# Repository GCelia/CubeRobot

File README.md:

# CubeRobot
Projet qui permet d'apprendre le routage sur Kicad ainsi que de coder sur platformIO en C

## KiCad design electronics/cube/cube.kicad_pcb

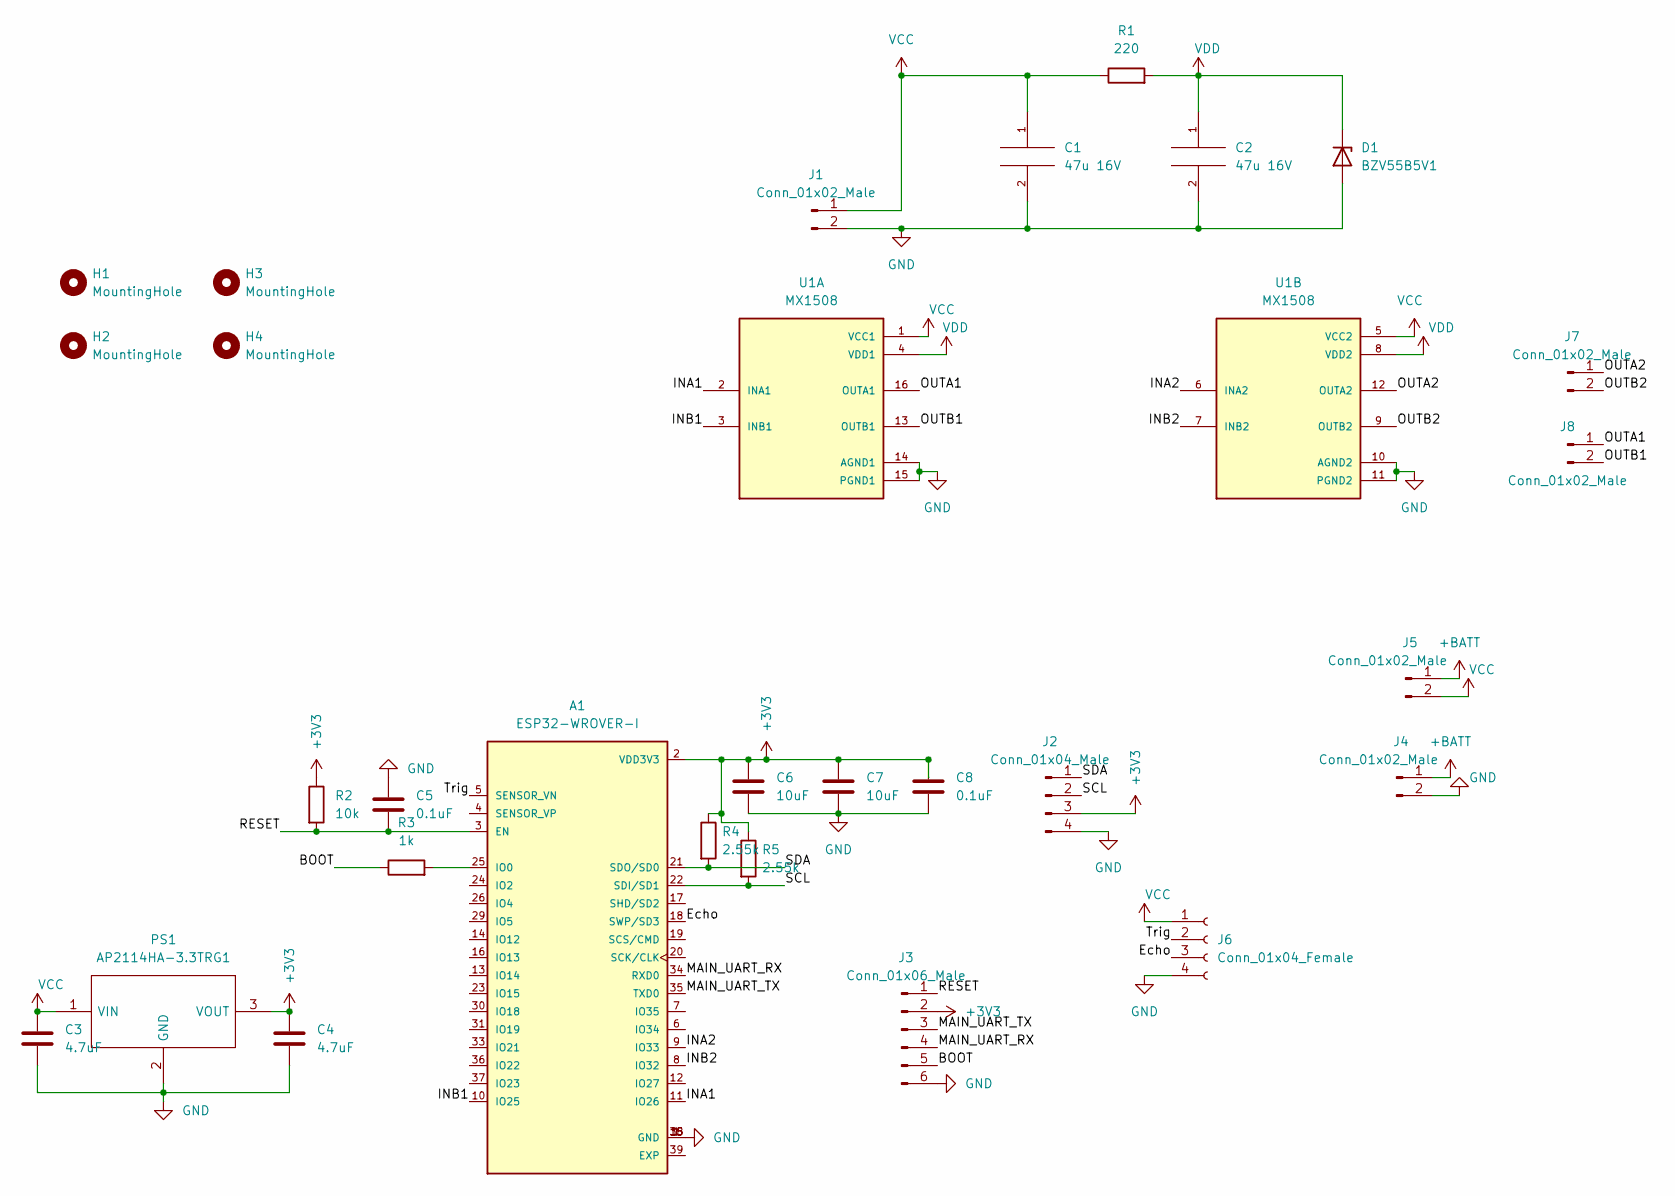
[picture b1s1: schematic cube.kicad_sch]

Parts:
A1: ESP32-WROVER-I; XCVR_ESP32-WROVER; DIGI-KEY_PART_NUMBER 1904-1008-1-ND
C1, C2: 47u 16V; CP_Elec_6.3x5.2
C3, C4: 4.7uF; C_0603_1608Metric_Pad1.08x0.95mm_HandSolder
C5, C8: 0.1uF; C_0603_1608Metric_Pad1.08x0.95mm_HandSolder
C6, C7: 10uF; C_0603_1608Metric_Pad1.08x0.95mm_HandSolder
D1: BZV55B5V1; D_1206_3216Metric_Pad1.42x1.75mm_HandSolder
H1, H2, H3, H4: MountingHole; MountingHole_2.2mm_M2_Pad_Via
J1, J4, J5, J7, J8: Conn_01x02_Male; PinHeader_1x02_P2.54mm_Vertical
J2: Conn_01x04_Male; PinHeader_1x04_P2.54mm_Vertical
J3: Conn_01x06_Male; PinHeader_1x06_P2.54mm_Vertical
J6: Conn_01x04_Female; PinHeader_1x04_P2.54mm_Vertical
PS1: AP2114HA-3.3TRG1; SOT-223-3_TabPin2; Manufacturer_Part_Number AP2114HA-3.3TRG1; Mouser Part Number 621-AP2114HA-3.3TRG1
R1: 220; R_0603_1608Metric_Pad0.98x0.95mm_HandSolder
R2: 10k; R_0603_1608Metric_Pad0.98x0.95mm_HandSolder
R3: 1k; R_0603_1608Metric_Pad0.98x0.95mm_HandSolder
R4, R5: 2.55k; R_0603_1608Metric_Pad0.98x0.95mm_HandSolder
U1: MX1508; SOIC127P600X177-16N

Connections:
+3V3: A1.2 (VDD3V3), C4.1, C6.1, C7.1, C8.1, J2.3, J3.2, PS1.3 (VOUT), R2.1, R4.1, R5.1
+BATT: J4.1, J5.1
/BOOT: J3.5, R3.1
/Echo: A1.18 (SWP/SD3), J6.3
/INA1: A1.11 (IO26), U1.2 (INA1)
/INA2: A1.9 (IO33), U1.6 (INA2)
/INB1: A1.10 (IO25), U1.3 (INB1)
/INB2: A1.8 (IO32), U1.7 (INB2)
/MAIN_UART_RX: A1.34 (RXD0), J3.4
/MAIN_UART_TX: A1.35 (TXD0), J3.3
/OUTA1: J8.1, U1.16 (OUTA1)
/OUTA2: J7.1, U1.12 (OUTA2)
/OUTB1: J8.2, U1.13 (OUTB1)
/OUTB2: J7.2, U1.9 (OUTB2)
/RESET: A1.3 (EN), C5.2, J3.1, R2.2
/SCL: A1.22 (SDI/SD1), J2.2, R5.2
/SDA: A1.21 (SDO/SD0), J2.1, R4.2
/Trig: A1.5 (SENSOR_VN), J6.2
GND: A1.1 (GND), A1.15 (GND), A1.38 (GND), C1.2, C2.2, C3.2, C4.2, C5.1, C6.2, C7.2, C8.2, D1.2 (A), J1.2, J2.4, J3.6, J4.2, J6.4, PS1.2 (GND), U1.10 (AGND2), U1.11 (PGND2), U1.14 (AGND1), U1.15 (PGND1)
unnamed: A1.25 (IO0), R3.2
VCC: C1.1, C3.1, J1.1, J5.2, J6.1, PS1.1 (VIN), R1.1, U1.1 (VCC1), U1.5 (VCC2)
VDD: C2.1, D1.1 (K), R1.2, U1.4 (VDD1), U1.8 (VDD2)

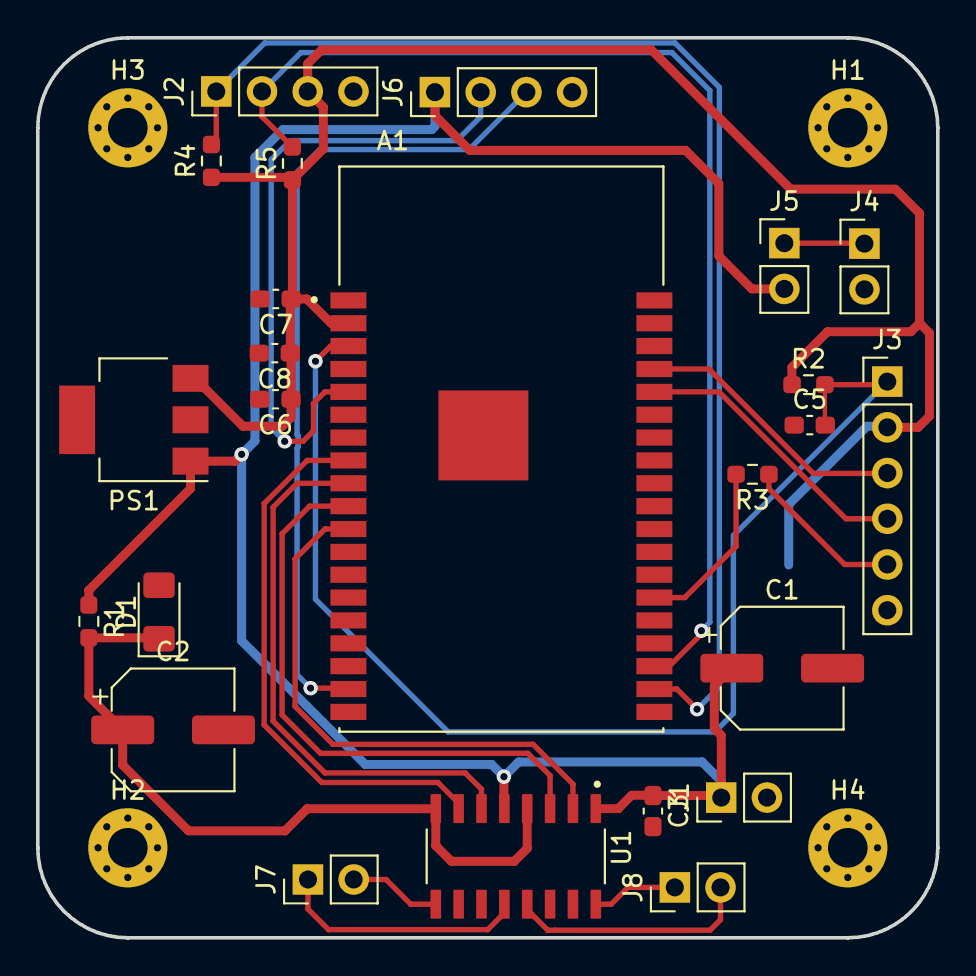
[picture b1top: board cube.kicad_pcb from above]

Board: 2 copper layers, 50.0 x 50.0 mm, 29 parts (1 on the bottom side), 22 nets.

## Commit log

2022-04-20 Ajout de la partie électronique
2022-04-20 added holes
2022-05-04 Added features + bugfixes
